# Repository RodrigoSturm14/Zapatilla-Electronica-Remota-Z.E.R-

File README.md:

#  Zapatilla Electrónica Remota (Z.E.R) ⚡🏠

# Descripción del proyecto
Este repositorio se dedica a documentar y recopilar el desarrollo de **Z.E.R**; un proyecto de automatizacion IoT desarrollado por Montial Octavio, Pierini Franco, Vallone Fabrizio, Sturm Rodrigo y Zuñiga Juan Jose.

Z.E.R es una zapatilla eléctrica que fue diseñada para activar y desactivar sus tomacorrientes inalámbricamente mediante nuestra aplicación móvil a través del uso de comunicación MQTT.
Decidimos implementar el protocolo de comunicacion MQTT debido a su sensillo uso y accecible conectividad WiFi con el microcontrolador ESP32.
Gracias a este proyecto, ampliamos nuestro conocimiento en diferentes areas como en el **desarrollo de Hardware**, **diseño de PCBs**, **desarrollo de Software (JavaScript - C++)** y **diseño 3D (SolidWork)**.

# Caracteristicas de Z.E.R
* **Microcontrolador ESP32** para hacer posible la conectividad IoT y un alto nivel de procesamiento.
* **Protocolo de comunicación MQTT** para la transmisión de datos a tiempo real.
* **Aplicación móvil** para una interfaz gráfica de usuario sencilla y accesible.
*  **Aprovisionamiento WiFi** para la conexión automática a redes WiFi.
* **Almacenamiento no volátil (NVS)** para guardar información temporalmente en la memoria flash del microcontrolador.
* **Sistema embebido unificado** para mayor ahorro de espacio y material.

#  Estructura del Repositorio
* **/Software**, se hayan las carpetas y los archivos de la programación móvil y del sistema embebido.
* **/Hardware**, se haya los recursos para observar el progreso del diseño del PCB.
* **/Diseño 3D**, se encuentran los archivos .STL  utilizados en el proyecto.

# Archivos Multimedia

## Fotos
### Aplicacion Movil

Aqui se muestra la estructura de la app. En la seccion superior puede verse el nombre del dispositivo, mientras que en el resto de la pantalla se situa la informacion de los diferentes tomas. Se tienen los siguientes elementos para controlar cada uno de los tomacorriente: 

* **Botones de encender y apagar**
* **Tabla indicativa del estado del toma** (Su color y mensaje cambia depende el estado).

### Diagramas de conexion con el broker

En este diagrama se ven las conexiones entre el broker y los nodos de la aplicacion movil y el microcontrolador. El broker MQTT es un intermediario en la comunicacion entre la aplicacion movil y el ESP32. Para que este protocolo funcione, ambas partes deben estar conectadas a una red WiFi.

### Interfaz grafica de conexiones en el broker

En esta imagen se ven representadas las conexiones que se realizan al usar el proyecto. El broker [Shiftr](https://www.shiftr.io/) permite ver un diagrama de conexiones a tiempo real de los clientes y los topicos. Por un lado, el "esp32-client" representa al microcontrolador de la zapatilla, el cual se encarga de recibir la informacion enviada por parte de la app. Esta ultima se ve en el otro extremo de la conexion. Por ultimo, se encuentran los "topicos" en donde se almacenan los mensajes enviados desde la app. Estos serian los tomas, y pueden adoptar un mensaje de "encendido" o "apagado".

### Placa Master 

En esta imagen se puede observar la placa principal del proyecto, la cual cumple el rol de recibir y confirmar este recibimiento los datos provenientes del broquer mqtt y encender o no cada uno de los tomas en consecuencia.
Principalmente está conformada por:
* **El microcontrolador Esp32:** Encargado de la comunicación con el broker mqtt y el proceso lógico en consecuencia
* **Los Relay:** Principales responsables del encendido y/o apagado de los tomas del proyecto.

### Placa de Periféricos:

En esta imagen se puede observar la placa secundaria del proyecto, la cual cumple el rol de mostrarle al usuario de forma visual el estado de conexión del dispositivo y una ruta de fácil acceso para poder reconfigurar este (conectar a una nueva red wifi). 
Principalmente está conformada por:
* **LEDs:** Quienes se encargan de mostrar si el dispositivo está conectado al Wifi, y de ser así, también otro para el caso del broquer mqtt.
* **Pulsador:** Perimite entrar al estado de configuración de Wifi en el caso de que este no pueda conectarse o de cambiar de ubicación el dispositivo.

## Videos

[Video](https://drive.google.com/file/d/11wxJRINLuGf1xzWTfpv2VvfbYe2Eymw4/view?usp=sharing)

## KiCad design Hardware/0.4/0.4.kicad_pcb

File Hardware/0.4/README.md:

# Placa Master

En esta imagen se puede observar la placa principal del proyecto, la cual cumple el rol de recibir y confirmar este recibimiento los datos provenientes del broquer mqtt y encender o no cada uno de los tomas en consecuencia.
Principalmente está conformada por:
* **El microcontrolador Esp32:** Encargado de la comunicación con el broker mqtt y el proceso lógico en consecuencia.
* **Los Relay:** Principales responsables del encendido y/o apagado de los tomas del proyecto.

## Funcionamiento:

Como se ve en el esquemático, la placa se separa en 4 partes:

### Esp32:

El cual permite la comunicacíon entre el broker mqtt y el la placa. Siendo el encargado de indicarle al resto de la placa las acciones a realizar.

### Relay:

Aqui se utiliza la señal generada por el microcontrolador para accionar los relay y encender o apagar cada tomacorriete. 
Para esto se utilizan 2 componentes cruciales:
* **El octoacoplador:** Quien separa las tenciones del microcontrolador de las de actuación del relay.
* **El transistor:** Quien permite accionar el relay utilizando la señal del octoacoblador:

### Alimentación:
Aqui se utiliza una fuente switching genérica de 5v 700mA para poder alimentar el proyecto utilizando directamente la red doméstica.

### Pulsador de configuracion Wifi:
Aquí se ubica una coneccion la cual permitirá comunicar la placa master con el periferico restante.

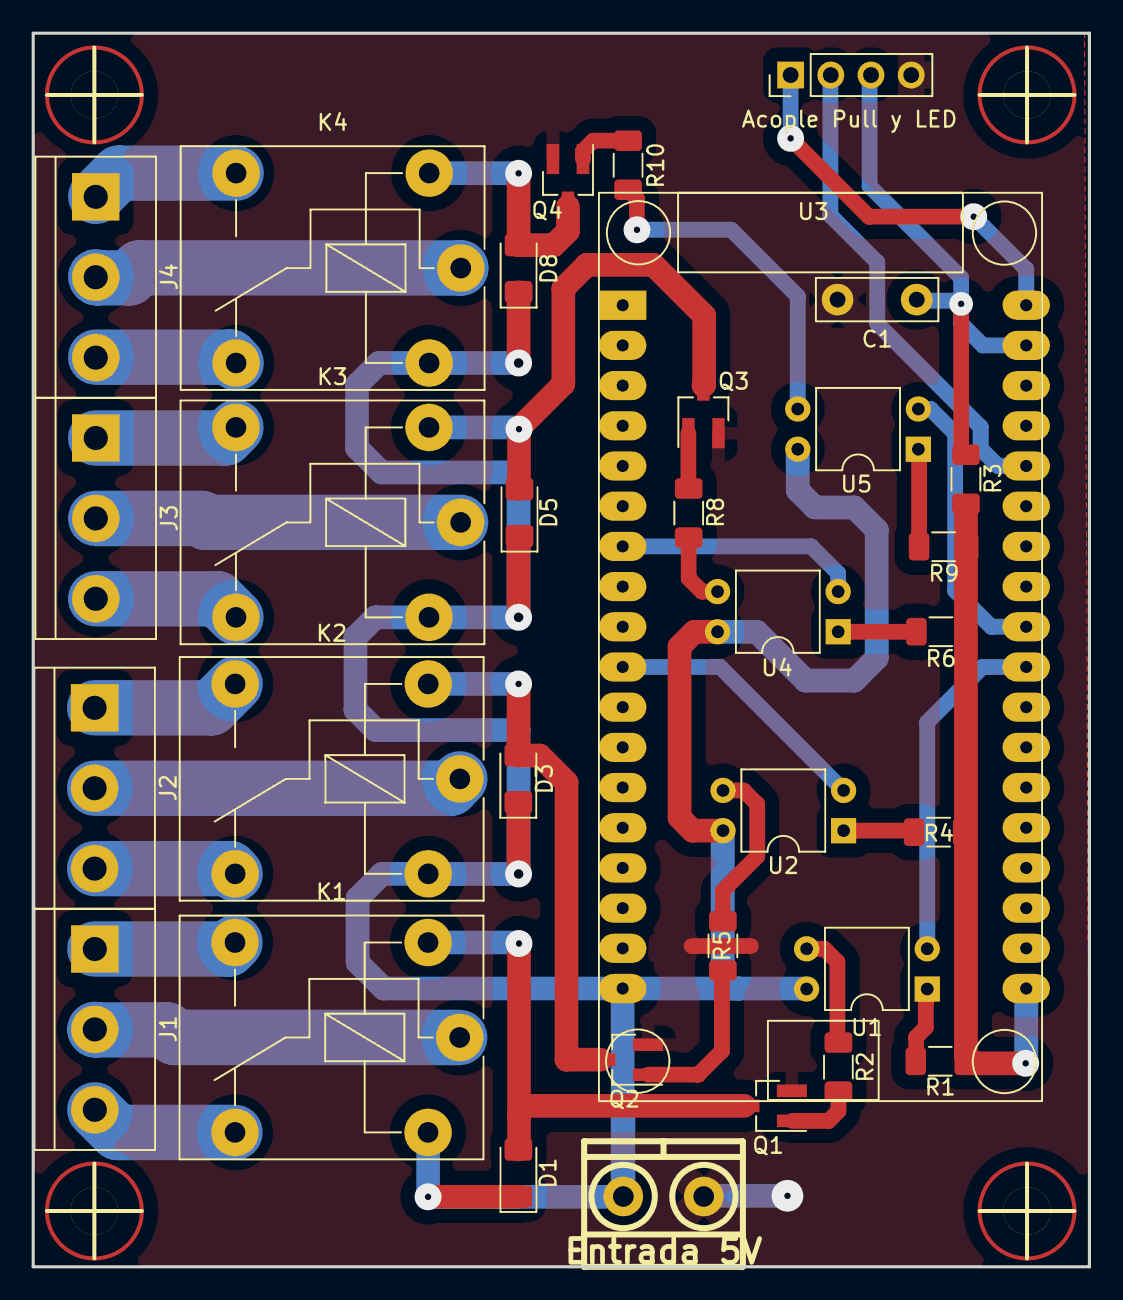
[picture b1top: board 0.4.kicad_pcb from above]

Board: 2 copper layers, 66.7 x 78.0 mm, 37 parts (0 on the bottom side), 38 nets.

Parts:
C1: C; C_Disc_D7.5mm_W2.5mm_P5.00mm
D1, D3, D5, D8: D_Shockley; D_1206_3216Metric_Pad1.42x1.75mm_HandSolder
J1: Relay1; TerminalBlock_bornier-3_P5.08mm
J2: Relay2; TerminalBlock_bornier-3_P5.08mm
J3: Relay3; TerminalBlock_bornier-3_P5.08mm
J4: Relay4; TerminalBlock_bornier-3_P5.08mm
J6: Entrada 5V; BORNERA2_AZUL
J7: Acople Pull y LED; PinHeader_1x04_P2.54mm_Vertical
K1, K2, K3, K4: G5V-1; Relay_SPDT_Finder_36.11
Q1, Q2, Q3, Q4: S8050; SOT-23_Handsoldering
R1, R2, R4, R5, R6, R8, R9, R10: 1k; R_1206_3216Metric_Pad1.30x1.75mm_HandSolder
R3: 4,7k; R_1206_3216Metric_Pad1.30x1.75mm_HandSolder
U1, U2, U4, U5: PC817; DIP-4_W7.62mm
U3: ESP32_DevKit_V1_DOIT; ESP32_Devkit_V1_36pin
hole_3mm, hole_3mm#2, hole_3mm#3, hole_3mm#4: VAL**; hole_3mm

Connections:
+3V3: R1.1, R3.1, R4.1, R6.1, R9.1, U3.19 (3V3)
+5V: D1.1 (K), D3.1 (K), D5.1 (K), D8.1 (K), J6.2, K1.2, K2.2, K3.2, K4.2, U1.4, U2.4, U3.18 (VIN), U4.4, U5.4
/BT_Config: C1.1, J7.3, R3.2, U3.35 (IO22)
/COM1: J1.2, K1.5
/COM2: J2.2, K2.5
/COM3: J3.2, K3.5
/COM4: J4.2, K4.5
/IN1: U1.2, U3.27 (RX2)
/IN2: U2.2, U3.10 (IO27)
/IN3: U3.7 (IO33), U4.2
/IN4: U3.28 (TX2), U5.2
/LED_ConfigBT: J7.1, U3.36 (IO23)
/LED_ConfigWIFI: J7.2, U3.32 (IO21)
/NC1: J1.3, K1.1
/NC2: J2.3, K2.1
/NC3: J3.3, K3.1
/NC4: J4.3, K4.1
/NO1: J1.1, K1.10
/NO2: J2.1, K2.10
/NO3: J3.1, K3.10
/NO4: J4.1, K4.10
GND: C1.2, J6.1, J7.4, Q1.2 (E), Q2.2 (E), Q3.2 (E), Q4.2 (E), U3.17 (GND)
unnamed: D1.2 (A), K1.9, Q1.3 (C)
unnamed: D3.2 (A), K2.9, Q2.3 (C)
unnamed: D5.2 (A), K3.9, Q3.3 (C)
unnamed: D8.2 (A), K4.9, Q4.3 (C)
unnamed: Q1.1 (B), R2.2
unnamed: Q2.1 (B), R5.2
unnamed: Q3.1 (B), R8.2
unnamed: Q4.1 (B), R10.2
unnamed: R1.2, U1.1
unnamed: R2.1, U1.3
unnamed: R4.2, U2.1
unnamed: R5.1, U2.3
unnamed: R6.2, U4.1
unnamed: R8.1, U4.3
unnamed: R9.2, U5.1
unnamed: R10.1, U5.3

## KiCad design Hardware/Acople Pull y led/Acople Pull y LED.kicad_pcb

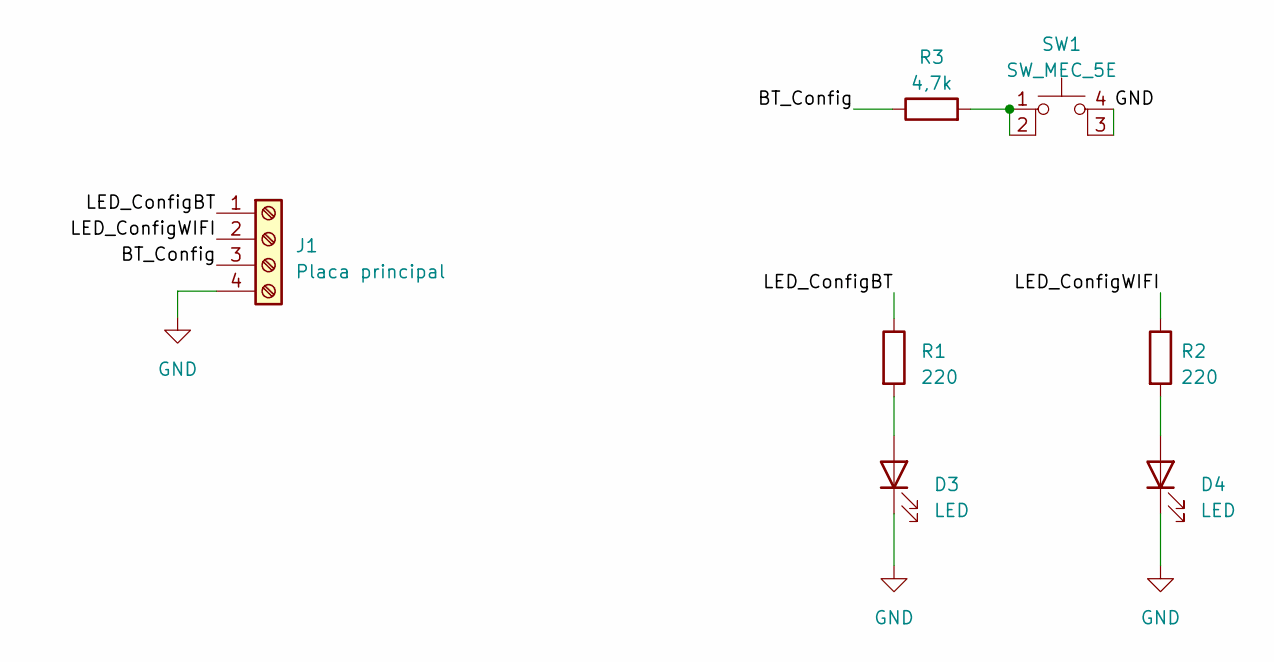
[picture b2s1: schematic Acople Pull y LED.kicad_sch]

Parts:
D3, D4: LED; LED_D3.0mm
J1: Placa principal; PinHeader_1x04_P2.54mm_Horizontal
R1, R2: 220; R_1206_3216Metric_Pad1.30x1.75mm_HandSolder
R3: 4,7k; R_1206_3216Metric_Pad1.30x1.75mm_HandSolder
SW1: SW_MEC_5E; Pulsador_TH_4

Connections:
/BT_Config: J1.3, R3.1
/LED_ConfigBT: J1.1, R1.1
/LED_ConfigWIFI: J1.2, R2.1
GND: D3.1 (K), D4.1 (K), J1.4, SW1.3 (K), SW1.4 (A)
unnamed: D3.2 (A), R1.2
unnamed: D4.2 (A), R2.2
unnamed: R3.2, SW1.1, SW1.2

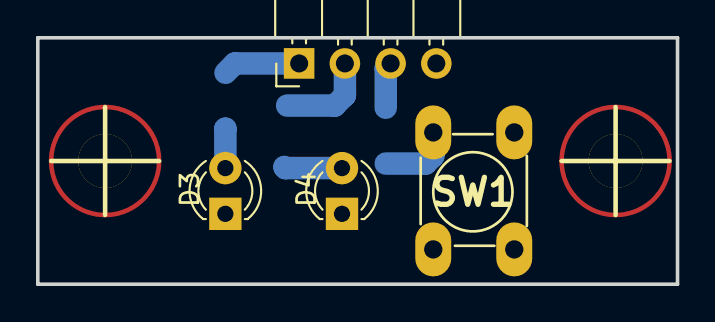
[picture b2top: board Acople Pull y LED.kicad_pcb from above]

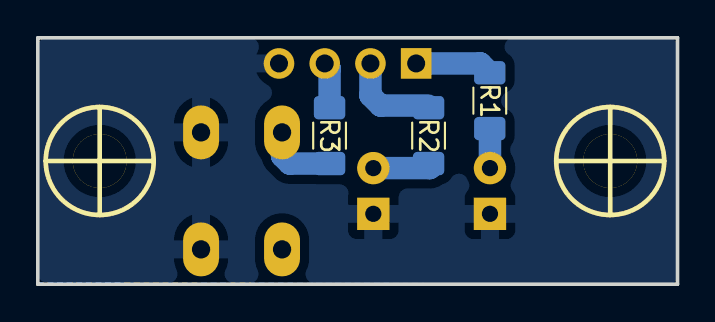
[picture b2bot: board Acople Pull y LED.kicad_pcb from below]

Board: 2 copper layers, 35.5 x 13.7 mm, 9 parts (3 on the bottom side), 7 nets.

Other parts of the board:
hole_3mm, hole_3mm#2: VAL**; hole_3mm

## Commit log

2023-11-13 Actualice archivo README.md
2023-11-13 Agregue archivo programacion ESP32
2023-11-13 Agregue archivo HTML para aprovisionamiento WiFi
2023-11-13 Agregue archivo HTML index
2023-11-13 Agregue archivo de estilos para WiFiManager
2023-11-13 Agregue imagen video a archivo README
2023-11-13 Agregue link de video a README
2023-11-13 Agregue link de video a archivo README.md
2023-11-14 CodigoAndroidStudio creado
2023-11-14 Create borrar despues
2023-11-14 Se ha subido el codigo de la app.
2023-11-15 Subir Archivos de Hardware y Modelos 3D del proyecto
2023-11-15 Update README.md
    Agregando sección relacionada con el hardware
2023-11-15 Agregue foto principal de la zapatilla a README.md
2023-11-15 Agregue diagrama de conexiones a README.md
2023-11-15 Agregue descripcion de diagrama a README.md
2023-11-15 Subiendo README de hardware
2023-11-15 Agregue emojis a README.md
2023-11-15 Subiendo imágenes esquemático master
2023-11-15 Subiendo imagen del esquematico general
2023-11-15 Update README.md
    Readme de placa master
2023-12-01 Elimine credenciales
